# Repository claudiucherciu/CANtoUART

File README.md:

# CAN to UART converter

## Overview
ATmega16M1 microcontroller, with 2 CAN transceivers and UART output.
Based on the Librecube LC-2601 design.

##TODO:

## Authors
* Claudiu Cherciu <claudiucherciu@gmail.com>
* Artur Scholz <artur.scholz@cubesat.de>

## Acknowledgements
Supported by the ESOC Cybernetic Club.

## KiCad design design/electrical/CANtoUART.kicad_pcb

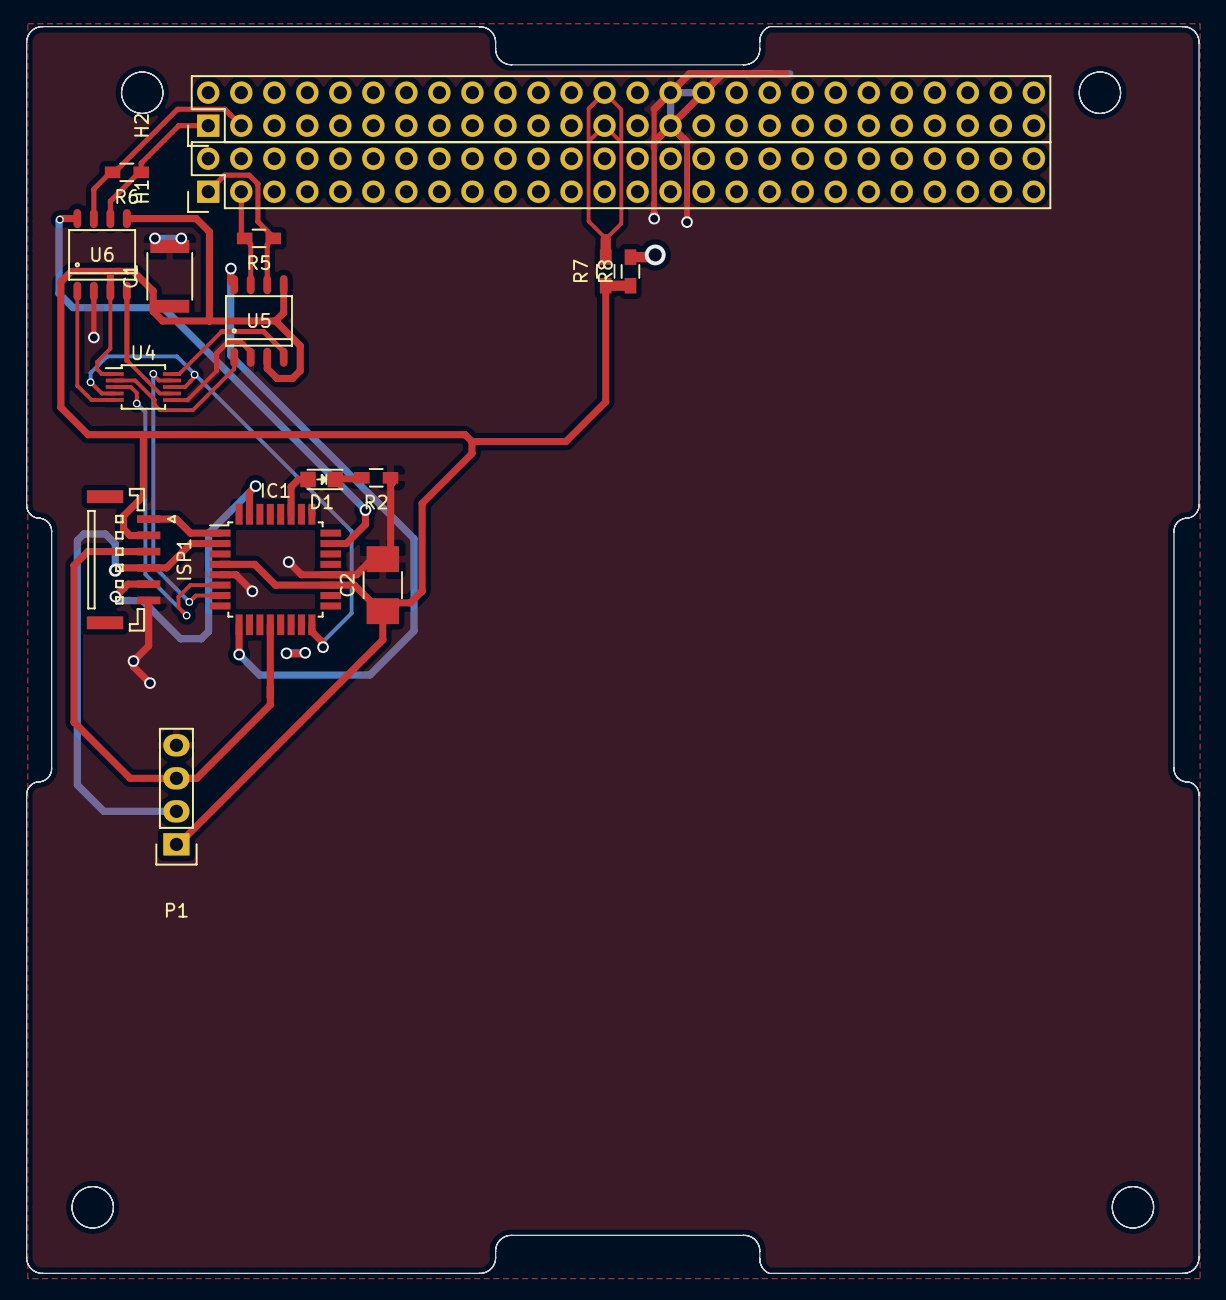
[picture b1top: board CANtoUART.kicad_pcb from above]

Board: 2 copper layers, 90.2 x 95.9 mm, 16 parts (0 on the bottom side), 22 nets.

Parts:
C1: 1 uF; C_1812
C2: x uF; C_1210_HandSoldering
D1: Led_Small; LED_0805
H1, H2: CONN_02X26; Pin_Header_Straight_2x26
IC1: ATMEGA16M1-A; TQFP-32_7x7mm_Pitch0.8mm
ISP1: CONN_01X06; JST_GH_BM06B-GHS-TBT_06x1.25mm_Straight
P1: CONN_01X04; Pin_Header_Straight_1x04
R2: 10k; R_0603_HandSoldering
R5, R6: 120; R_0603_HandSoldering
R7: 0; R_0603_HandSoldering
R8: DNP; R_0603_HandSoldering
U4: ADG787; MSOP-10_3x3mm_Pitch0.5mm
U5, U6: ATA6561; SO-8

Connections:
5V_BUS: H2.25, H2.26, R7.2
+5V: C1.1, C2.1, IC1.4, IC1.19, ISP1.2, P1.1, R7.1, R8.1, U4.1, U5.3, U5.5, U6.3, U6.5
CAN1_H: H1.3, R5.2, U5.7
CAN1_L: H1.1, R5.1, U5.6
CAN1_STBY: IC1.9, U5.8
CAN2_H: H2.3, R6.2, U6.7
CAN2_L: H2.1, R6.1, U6.6
CAN2_STBY: IC1.23, U6.8
CAN_SEL: IC1.16, U4.4, U4.8
GND: C1.2, C2.2, H2.29, H2.30, H2.32, IC1.5, IC1.20, ISP1.6, P1.4, R2.1, U4.6, U5.2, U6.2
unnamed: D1.1, R2.2
unnamed: D1.2, IC1.27
unnamed: IC1.1, ISP1.1
unnamed: IC1.31, ISP1.5
unnamed: U4.2, U5.1
unnamed: U4.5, U6.1
unnamed: U4.7, U6.4
unnamed: U4.10, U5.4
RX_CAN: IC1.7, U4.9
TX_CAN: IC1.6, U4.3
uC_RX: IC1.12, ISP1.3, P1.3
uC_TX: IC1.2, ISP1.4, P1.2

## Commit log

2016-10-13 First correct upload. Disregard previous files.
